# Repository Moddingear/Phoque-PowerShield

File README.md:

# Phoque Power Shield

This is an example shield for the Phoque-series of brushless drivers. Includes:
- XT60 connector
- 2.8Ohm configurable PCB resistor (can overheat, be careful, shouldn't be left on)
- Extra capacitors (Recommend JIERR PA63V470M10X17 for the through-hole)

This shield can be connected to the main board using 4mm M3 brass standoffs.

Feel free to modify to suit your needs.

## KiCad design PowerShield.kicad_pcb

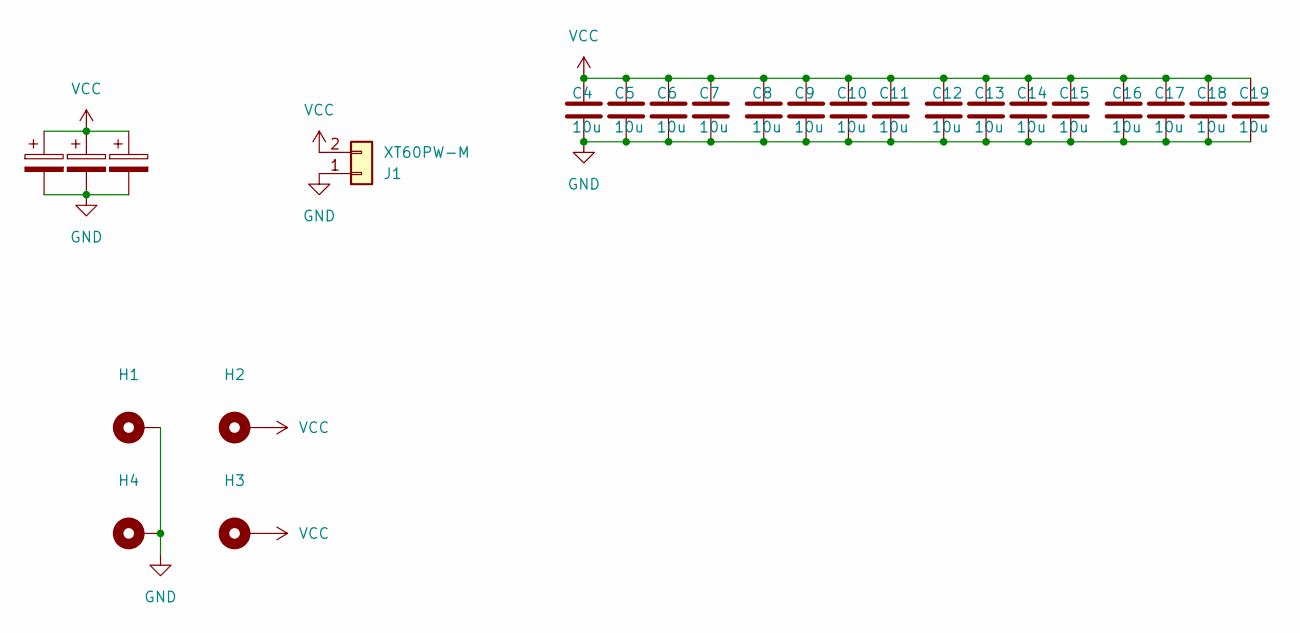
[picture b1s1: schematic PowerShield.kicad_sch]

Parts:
C1, C2, C3: C_Polarized; CP_Radial_D10.0mm_P5.00mm
C4, C5, C6, C7, C8, C9, C10, C11, C12, C13, C14, C15, C16, C17, C18, C19: 10u; C_0805_2012Metric
H1, H2, H3, H4: MountingHole_Pad; MountingHole_3.2mm_M3_Pad_Via
J1: XT60PW-M; AMASS_XT60PW-M_1x02_P7.20mm_Horizontal

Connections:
GND: C1.2, C2.2, C3.2, C4.2, C5.2, C6.2, C7.2, C8.2, C9.2, C10.2, C11.2, C12.2, C13.2, C14.2, C15.2, C16.2, C17.2, C18.2, C19.2, H1.1, H4.1, J1.1
VCC: C1.1, C2.1, C3.1, C4.1, C5.1, C6.1, C7.1, C8.1, C9.1, C10.1, C11.1, C12.1, C13.1, C14.1, C15.1, C16.1, C17.1, C18.1, C19.1, H2.1, H3.1, J1.2

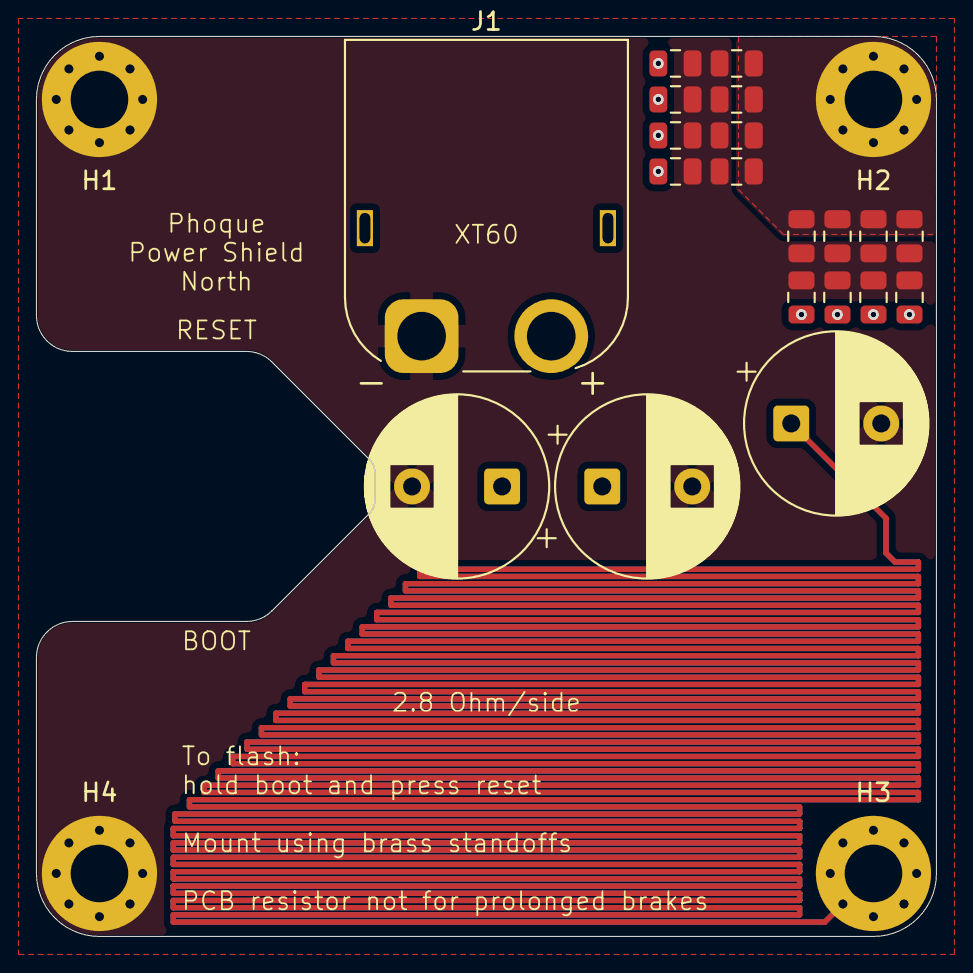
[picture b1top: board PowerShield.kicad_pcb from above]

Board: 2 copper layers, 50.0 x 50.0 mm, 24 parts (0 on the bottom side), 2 nets.

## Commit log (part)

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2026-05-22 Create LICENSE
